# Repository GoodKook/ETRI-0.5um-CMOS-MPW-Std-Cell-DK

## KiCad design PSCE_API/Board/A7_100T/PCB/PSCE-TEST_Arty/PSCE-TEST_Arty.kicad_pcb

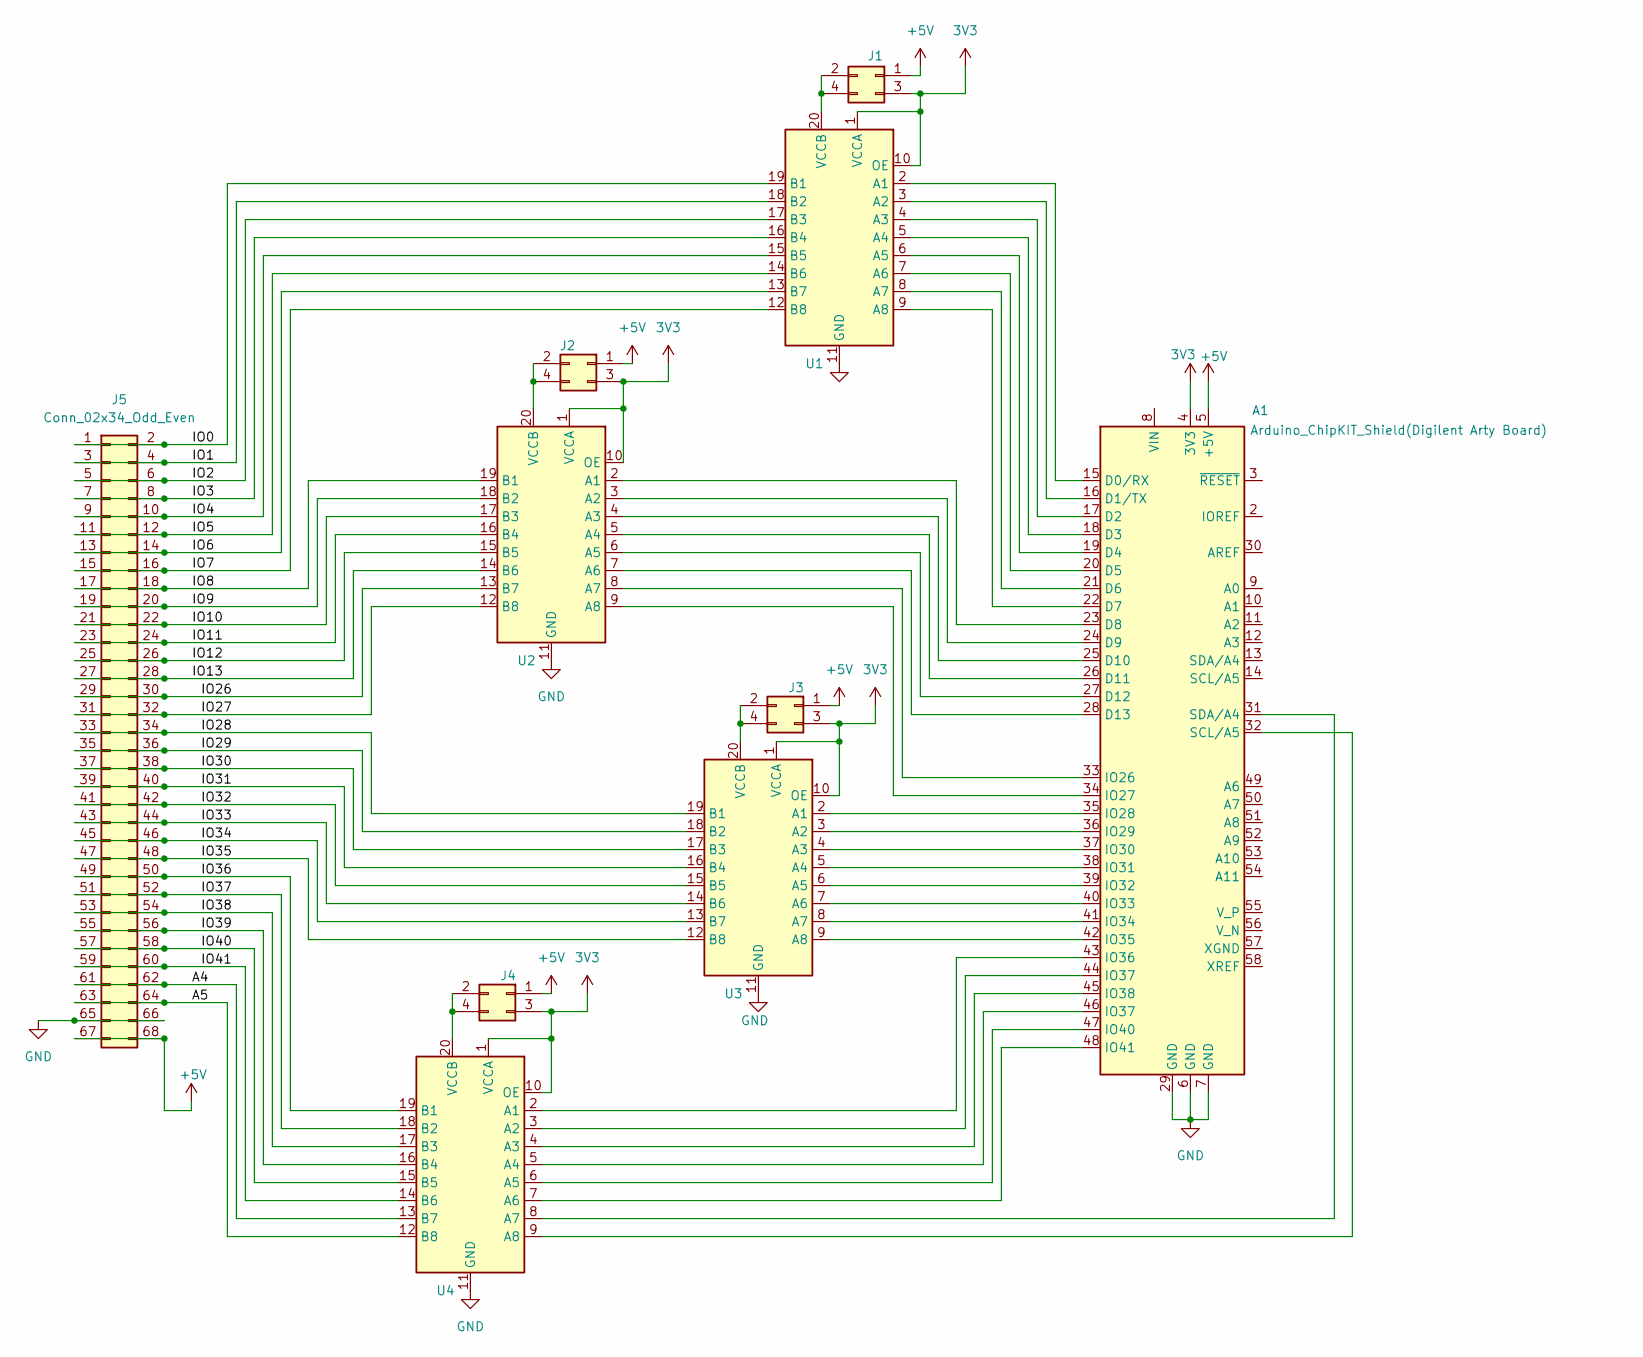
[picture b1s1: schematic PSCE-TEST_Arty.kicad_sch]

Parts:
A1: Arduino_ChipKIT_Shield(Digilent Arty Board); Arduino_ChipKIT_Shield
J1, J2, J3, J4: Conn_02x02_Odd_Even; PinHeader_2x02_P2.54mm_Vertical
J5: Conn_02x34_Odd_Even; PinHeader_2x34_P2.54mm_Vertical
U1, U2, U3, U4: Level_Shifter_Module_HW-221

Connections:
3V3: A1.4 (3V3), J1.3, J2.3, J3.3, J4.3, U1.1 (VCCA), U1.10 (OE), U2.1 (VCCA), U2.10 (OE), U3.1 (VCCA), U3.10 (OE), U4.1 (VCCA), U4.10 (OE)
+5V: A1.5 (+5V), J1.1, J2.1, J3.1, J4.1, J5.67, J5.68
/A4: J5.61, J5.62, U4.13 (B7)
/A5: J5.63, J5.64, U4.12 (B8)
/IO0: J5.1, J5.2, U1.19 (B1)
/IO1: J5.3, J5.4, U1.18 (B2)
/IO2: J5.5, J5.6, U1.17 (B3)
/IO3: J5.7, J5.8, U1.16 (B4)
/IO4: J5.9, J5.10, U1.15 (B5)
/IO5: J5.11, J5.12, U1.14 (B6)
/IO6: J5.13, J5.14, U1.13 (B7)
/IO7: J5.15, J5.16, U1.12 (B8)
/IO8: J5.17, J5.18, U2.19 (B1)
/IO9: J5.19, J5.20, U2.18 (B2)
/IO10: J5.21, J5.22, U2.17 (B3)
/IO11: J5.23, J5.24, U2.16 (B4)
/IO12: J5.25, J5.26, U2.15 (B5)
/IO13: J5.27, J5.28, U2.14 (B6)
/IO26: J5.29, J5.30, U2.13 (B7)
/IO27: J5.31, J5.32, U2.12 (B8)
/IO28: J5.33, J5.34, U3.19 (B1)
/IO29: J5.35, J5.36, U3.18 (B2)
/IO30: J5.37, J5.38, U3.17 (B3)
/IO31: J5.39, J5.40, U3.16 (B4)
/IO32: J5.41, J5.42, U3.15 (B5)
/IO33: J5.43, J5.44, U3.14 (B6)
/IO34: J5.45, J5.46, U3.13 (B7)
/IO35: J5.47, J5.48, U3.12 (B8)
/IO36: J5.49, J5.50, U4.19 (B1)
/IO37: J5.51, J5.52, U4.18 (B2)
/IO38: J5.53, J5.54, U4.17 (B3)
/IO39: J5.55, J5.56, U4.16 (B4)
/IO40: J5.57, J5.58, U4.15 (B5)
/IO41: J5.59, J5.60, U4.14 (B6)
GND: A1.6 (GND), A1.7 (GND), A1.29 (GND), J5.65, J5.66, U1.11 (GND), U2.11 (GND), U3.11 (GND), U4.11 (GND)
unnamed: A1.15 (D0/RX), U1.2 (A1)
unnamed: A1.16 (D1/TX), U1.3 (A2)
unnamed: A1.17 (D2), U1.4 (A3)
unnamed: A1.18 (D3), U1.5 (A4)
unnamed: A1.19 (D4), U1.6 (A5)
unnamed: A1.20 (D5), U1.7 (A6)
unnamed: A1.21 (D6), U1.8 (A7)
unnamed: A1.22 (D7), U1.9 (A8)
unnamed: A1.23 (D8), U2.2 (A1)
unnamed: A1.24 (D9), U2.3 (A2)
unnamed: A1.25 (D10), U2.4 (A3)
unnamed: A1.26 (D11), U2.5 (A4)
unnamed: A1.27 (D12), U2.6 (A5)
unnamed: A1.28 (D13), U2.7 (A6)
unnamed: A1.33 (IO26), U2.8 (A7)
unnamed: A1.34 (IO27), U2.9 (A8)
unnamed: A1.35 (IO28), U3.2 (A1)
unnamed: A1.36 (IO29), U3.3 (A2)
unnamed: A1.37 (IO30), U3.4 (A3)
unnamed: A1.38 (IO31), U3.5 (A4)
unnamed: A1.39 (IO32), U3.6 (A5)
unnamed: A1.40 (IO33), U3.7 (A6)
unnamed: A1.41 (IO34), U3.8 (A7)
unnamed: A1.42 (IO35), U3.9 (A8)
unnamed: A1.43 (IO36), U4.2 (A1)
unnamed: A1.45 (IO38), U4.4 (A3)
unnamed: A1.47 (IO40), U4.6 (A5)
unnamed: A1.48 (IO41), U4.7 (A6)
unnamed: J1.2, J1.4, U1.20 (VCCB)
unnamed: J2.2, J2.4, U2.20 (VCCB)
unnamed: J3.2, J3.4, U3.20 (VCCB)
unnamed: J4.2, J4.4, U4.20 (VCCB)
unnamed: A1.44 (IO37), U4.3 (A2)
unnamed: A1.46 (IO37), U4.5 (A4)
unnamed: A1.31 (SDA/A4), U4.8 (A7)
unnamed: A1.32 (SCL/A5), U4.9 (A8)

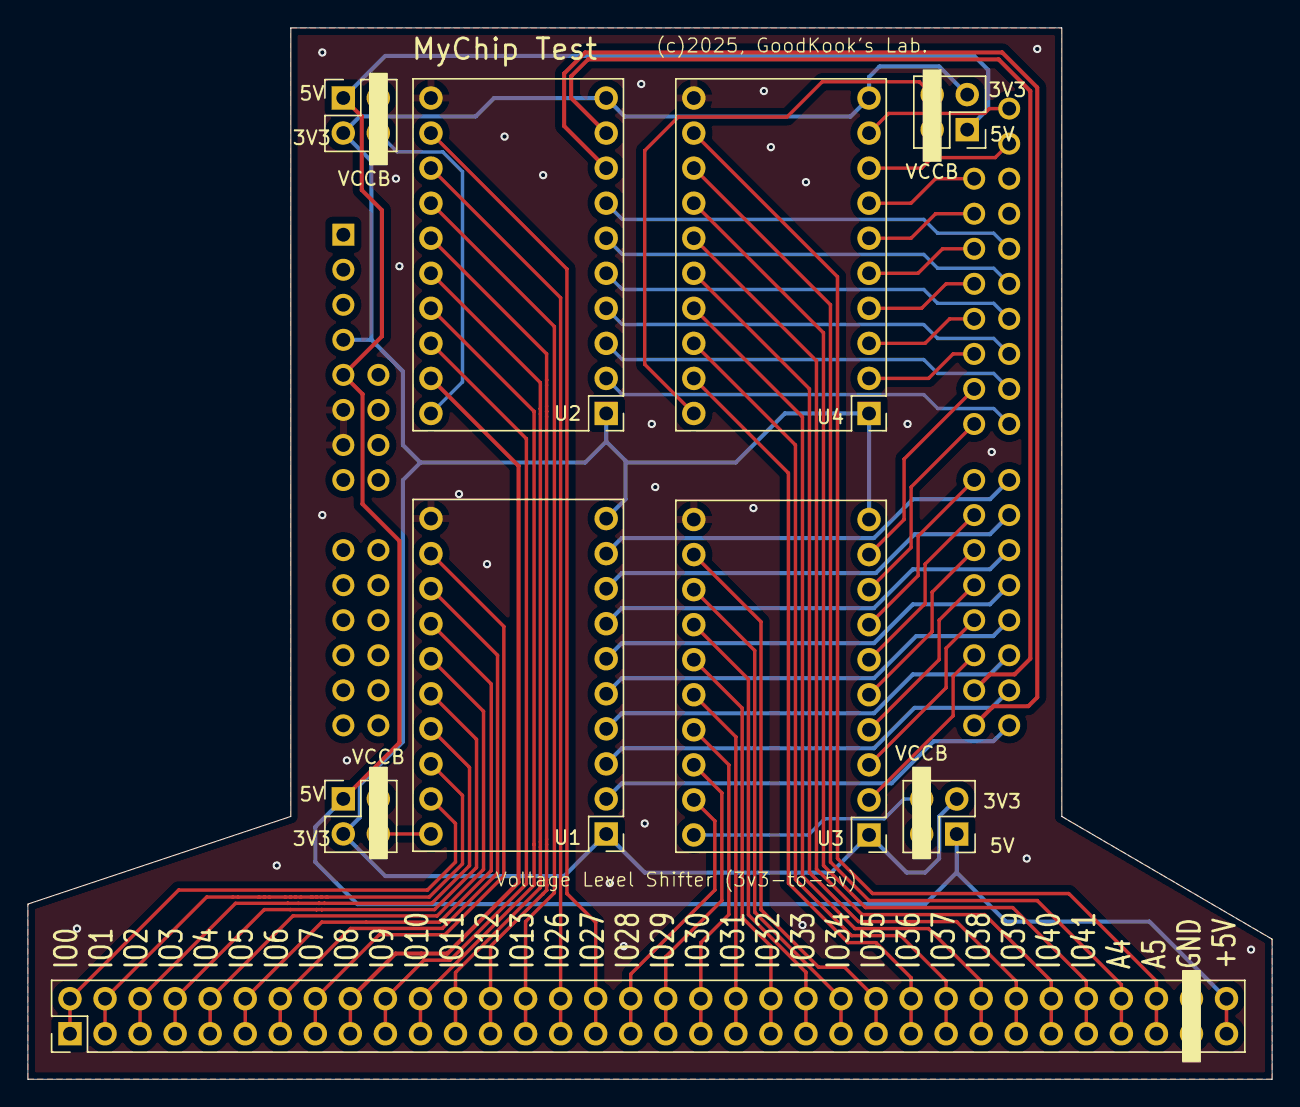
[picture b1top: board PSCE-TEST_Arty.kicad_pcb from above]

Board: 2 copper layers, 90.2 x 76.2 mm, 10 parts (0 on the bottom side), 71 nets.

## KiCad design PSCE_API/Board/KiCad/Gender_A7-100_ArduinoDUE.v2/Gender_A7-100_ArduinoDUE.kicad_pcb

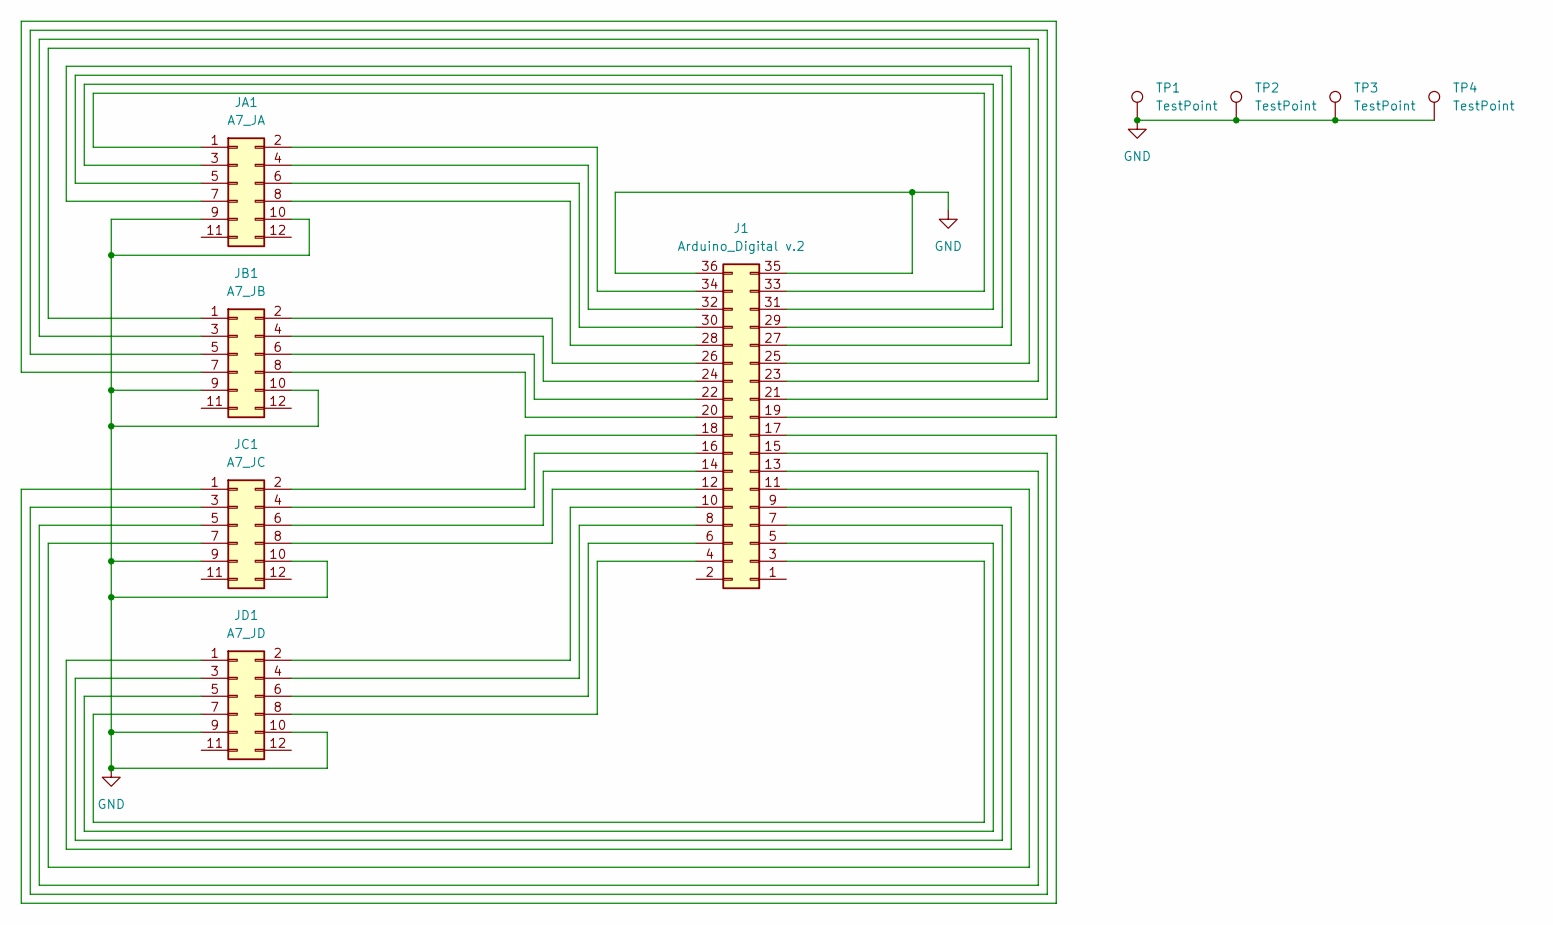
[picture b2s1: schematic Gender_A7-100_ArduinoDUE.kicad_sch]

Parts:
J1: Arduino_Digital v.2; PinHeader_2x18_P2.54mm_Vertical
JA1: A7_JA; PinHeader_2x06_P2.54mm_Vertical
JB1: A7_JB; PinHeader_2x06_P2.54mm_Vertical
JC1: A7_JC; PinHeader_2x06_P2.54mm_Vertical
JD1: A7_JD; PinHeader_2x06_P2.54mm_Vertical
TP1, TP2, TP4: TestPoint; TestPoint_Plated_Hole_D4.0mm
TP3: TestPoint; TestPoint_Bridge_Pitch7.62mm_Drill1.3mm

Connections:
GND: J1.35, J1.36, JA1.9, JA1.10, JB1.9, JB1.10, JC1.9, JC1.10, JD1.9, JD1.10, TP1.1, TP2.1, TP3.1, TP4.1
unnamed: J1.3, JD1.7
unnamed: J1.4, JD1.8
unnamed: J1.5, JD1.5
unnamed: J1.6, JD1.6
unnamed: J1.7, JD1.3
unnamed: J1.8, JD1.4
unnamed: J1.9, JD1.1
unnamed: J1.10, JD1.2
unnamed: J1.11, JC1.7
unnamed: J1.12, JC1.8
unnamed: J1.13, JC1.5
unnamed: J1.14, JC1.6
unnamed: J1.15, JC1.3
unnamed: J1.16, JC1.4
unnamed: J1.17, JC1.1
unnamed: J1.18, JC1.2
unnamed: J1.19, JB1.7
unnamed: J1.20, JB1.8
unnamed: J1.21, JB1.5
unnamed: J1.22, JB1.6
unnamed: J1.23, JB1.3
unnamed: J1.24, JB1.4
unnamed: J1.25, JB1.1
unnamed: J1.26, JB1.2
unnamed: J1.27, JA1.7
unnamed: J1.28, JA1.8
unnamed: J1.29, JA1.5
unnamed: J1.30, JA1.6
unnamed: J1.31, JA1.3
unnamed: J1.32, JA1.4
unnamed: J1.33, JA1.1
unnamed: J1.34, JA1.2

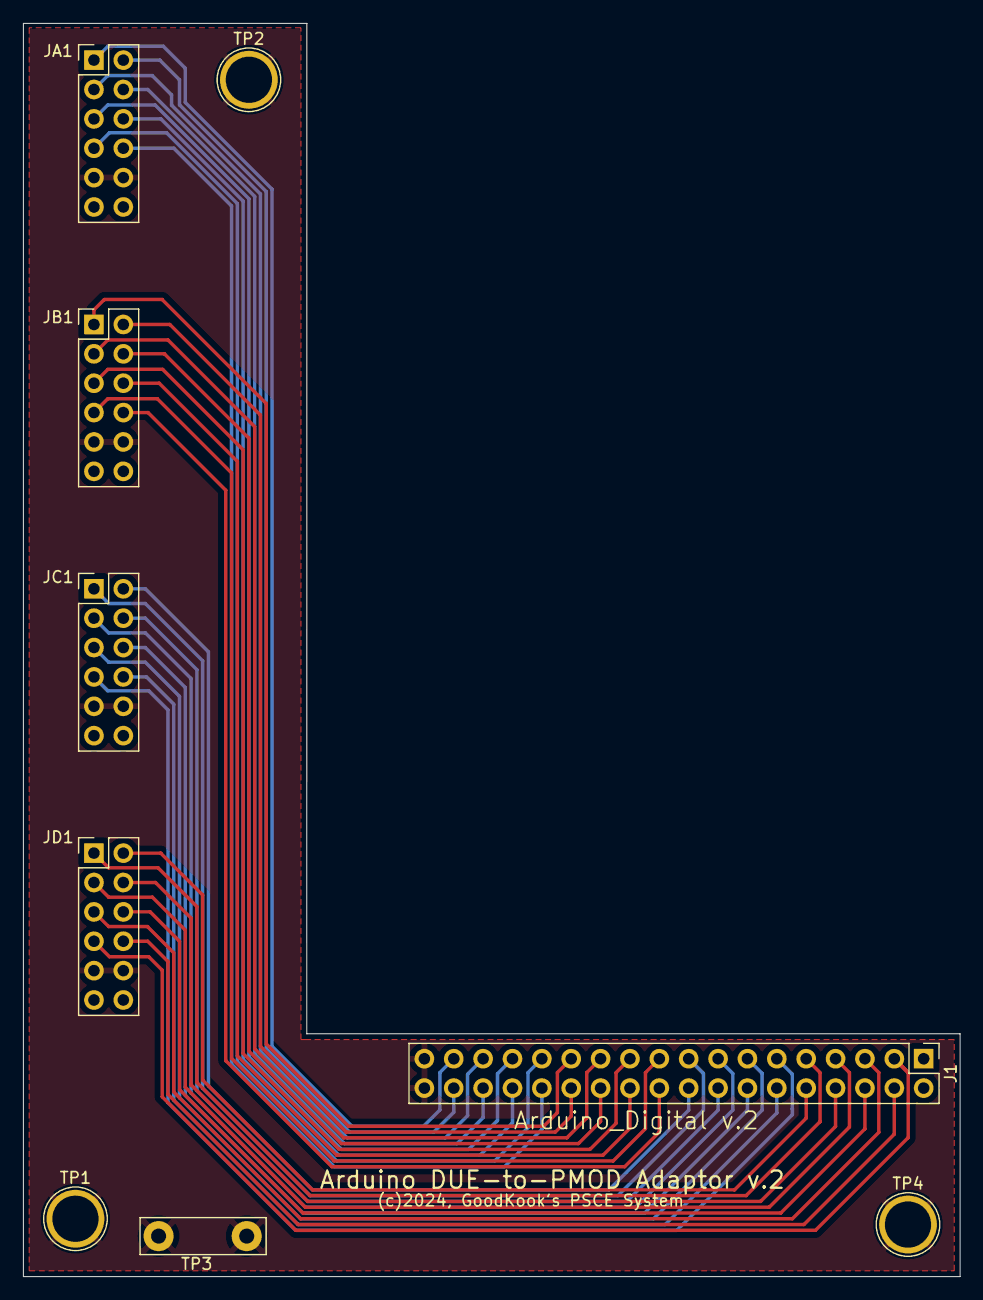
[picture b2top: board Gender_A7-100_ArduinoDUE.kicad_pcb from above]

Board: 2 copper layers, 81.0 x 108.4 mm, 9 parts (0 on the bottom side), 33 nets.

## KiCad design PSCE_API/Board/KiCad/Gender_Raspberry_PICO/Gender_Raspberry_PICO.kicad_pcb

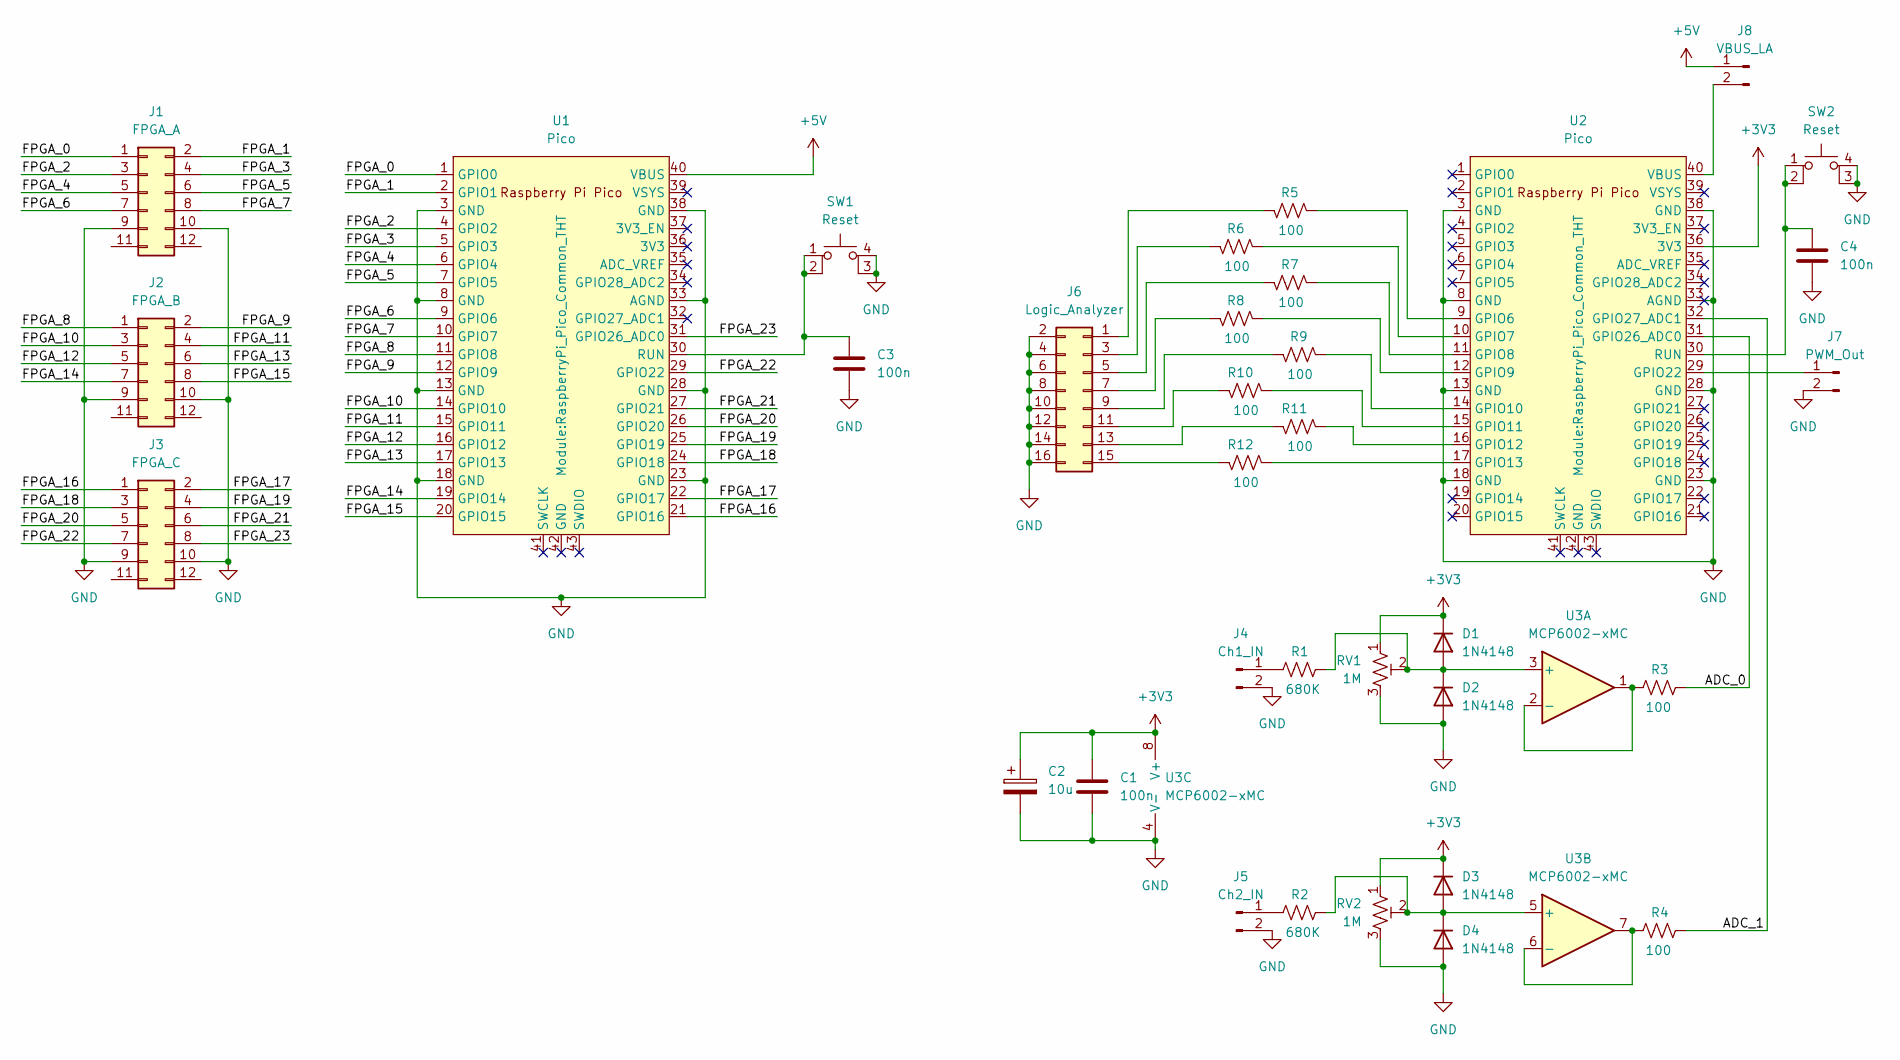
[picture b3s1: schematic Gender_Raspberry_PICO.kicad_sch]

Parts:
C1, C3, C4: 100n; C_Disc_D3.8mm_W2.6mm_P2.50mm
C2: 10u; CP_Radial_Tantal_D9.0mm_P2.50mm
D1, D2, D3, D4: 1N4148; D_DO-35_SOD27_P7.62mm_Horizontal
J1: FPGA_A; PinHeader_2x06_P2.54mm_Vertical
J2: FPGA_B; PinHeader_2x06_P2.54mm_Vertical
J3: FPGA_C; PinHeader_2x06_P2.54mm_Vertical
J4: Ch1_IN; PinHeader_2x01_P2.54mm_Vertical
J5: Ch2_IN; PinHeader_2x01_P2.54mm_Vertical
J6: Logic_Analyzer; PinHeader_2x08_P2.54mm_Vertical
J7: PWM_Out; PinHeader_2x01_P2.54mm_Vertical
J8: VBUS_LA; PinHeader_2x01_P2.54mm_Vertical
R1, R2: 680K; R_Axial_DIN0204_L3.6mm_D1.6mm_P7.62mm_Horizontal
R3, R4, R5, R6, R7, R8, R9, R10, R11, R12: 100; R_Axial_DIN0204_L3.6mm_D1.6mm_P7.62mm_Horizontal
RV1, RV2: 1M; Potentiometer_Runtron_RM-065_Vertical
SW1, SW2: Reset; SW_PUSH_6mm_H9.5mm
U1, U2: Pico; RaspberryPi_Pico_Common_THT
U3: MCP6002-xMC; DIP-8_W10.16mm_LongPads

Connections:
+3V3: C1.1, C2.1, D1.1 (K), D3.1 (K), RV1.1, RV2.1, U2.36 (3V3), U3.8 (V+)
+5V: J8.1, U1.40 (VBUS)
/ADC_0: R3.1, U2.31 (GPIO26_ADC0)
/ADC_1: R4.1, U2.32 (GPIO27_ADC1)
/FPGA_0: J1.1, U1.1 (GPIO0)
/FPGA_1: J1.2, U1.2 (GPIO1)
/FPGA_2: J1.3, U1.4 (GPIO2)
/FPGA_3: J1.4, U1.5 (GPIO3)
/FPGA_4: J1.5, U1.6 (GPIO4)
/FPGA_5: J1.6, U1.7 (GPIO5)
/FPGA_6: J1.7, U1.9 (GPIO6)
/FPGA_7: J1.8, U1.10 (GPIO7)
/FPGA_8: J2.1, U1.11 (GPIO8)
/FPGA_9: J2.2, U1.12 (GPIO9)
/FPGA_10: J2.3, U1.14 (GPIO10)
/FPGA_11: J2.4, U1.15 (GPIO11)
/FPGA_12: J2.5, U1.16 (GPIO12)
/FPGA_13: J2.6, U1.17 (GPIO13)
/FPGA_14: J2.7, U1.19 (GPIO14)
/FPGA_15: J2.8, U1.20 (GPIO15)
/FPGA_16: J3.1, U1.21 (GPIO16)
/FPGA_17: J3.2, U1.22 (GPIO17)
/FPGA_18: J3.3, U1.24 (GPIO18)
/FPGA_19: J3.4, U1.25 (GPIO19)
/FPGA_20: J3.5, U1.26 (GPIO20)
/FPGA_21: J3.6, U1.27 (GPIO21)
/FPGA_22: J3.7, U1.29 (GPIO22)
/FPGA_23: J3.8, U1.31 (GPIO26_ADC0)
GND: C1.2, C2.2, C3.2, C4.2, D2.2 (A), D4.2 (A), J1.9, J1.10, J2.9, J2.10, J3.9, J3.10, J4.2, J5.2, J6.2, J6.4, J6.6, J6.8, J6.10, J6.12, J6.14, J6.16, J7.2, RV1.3, RV2.3, SW1.3 (K), SW1.4 (A), SW2.3 (K), SW2.4 (A), U1.3 (GND), U1.8 (GND), U1.13 (GND), U1.18 (GND), U1.23 (GND), U1.28 (GND), U1.33 (AGND), U1.38 (GND), U2.3 (GND), U2.8 (GND), U2.13 (GND), U2.18 (GND), U2.23 (GND), U2.28 (GND), U2.33 (AGND), U2.38 (GND), U3.4 (V-), U3.9 (V-)
unnamed: D1.2 (A), D2.1 (K), R1.1, RV1.2, U3.3 (+)
unnamed: D3.2 (A), D4.1 (K), R2.1, RV2.2, U3.5 (+)
unnamed: J4.1, R1.2
unnamed: J5.1, R2.2
unnamed: J6.1, R5.1
unnamed: J6.3, R6.1
unnamed: J6.5, R7.1
unnamed: J6.7, R8.1
unnamed: J6.9, R9.1
unnamed: J6.11, R10.1
unnamed: J6.13, R11.1
unnamed: J6.15, R12.1
unnamed: J7.1, U2.29 (GPIO22)
unnamed: J8.2, U2.40 (VBUS)
unnamed: C3.1, SW1.1, SW1.2, U1.30 (RUN)
unnamed: R5.2, U2.9 (GPIO6)
unnamed: R6.2, U2.10 (GPIO7)
unnamed: R7.2, U2.11 (GPIO8)
unnamed: R8.2, U2.12 (GPIO9)
unnamed: R9.2, U2.14 (GPIO10)
unnamed: R10.2, U2.15 (GPIO11)
unnamed: R11.2, U2.16 (GPIO12)
unnamed: R12.2, U2.17 (GPIO13)
unnamed: C4.1, SW2.1, SW2.2, U2.30 (RUN)
unnamed: R3.2, U3.1, U3.2 (-)
unnamed: R4.2, U3.6 (-), U3.7

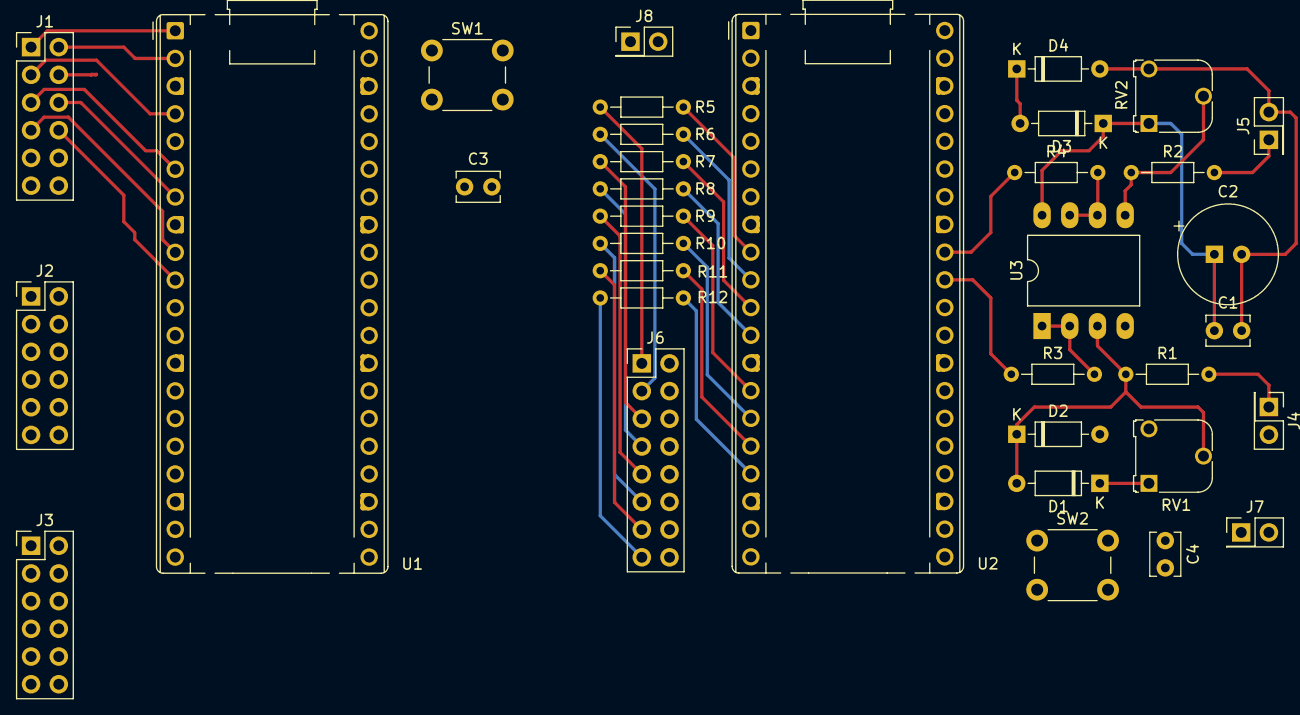
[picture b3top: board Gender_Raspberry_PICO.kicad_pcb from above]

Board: 2 copper layers, 35 parts (0 on the bottom side), 55 nets.

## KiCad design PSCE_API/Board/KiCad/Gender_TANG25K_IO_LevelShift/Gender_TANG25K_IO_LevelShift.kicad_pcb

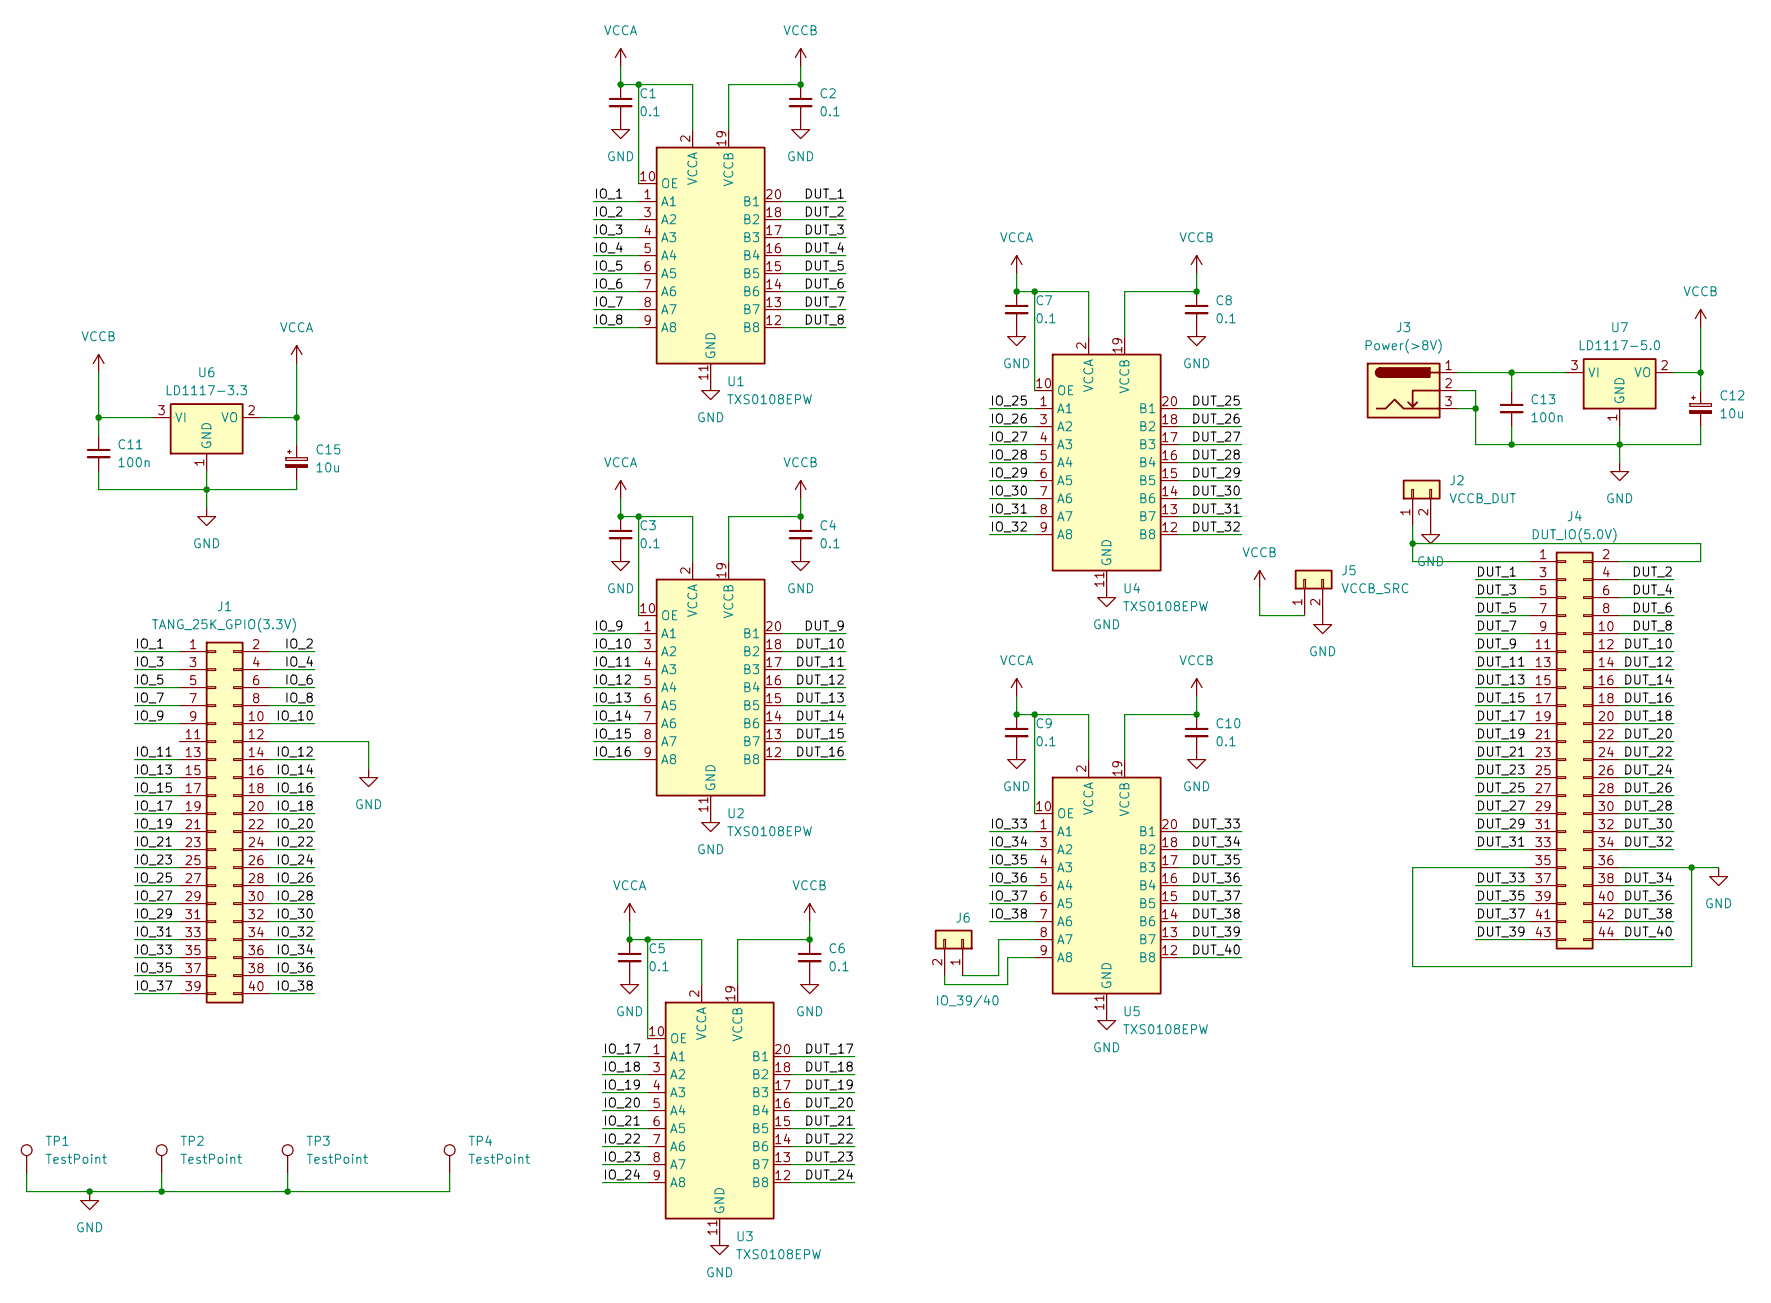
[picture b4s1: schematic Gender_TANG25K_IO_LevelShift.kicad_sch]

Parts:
C1, C2, C3, C4, C5, C6, C7, C8, C9, C10: 0.1; C_0805_2012Metric
C11, C13: 100n; C_0805_2012Metric
C12, C15: 10u; CP_Radial_D6.3mm_P2.50mm
J1: TANG_25K_GPIO(3.3V); PinHeader_2x20_P2.54mm_Vertical
J2: VCCB_DUT; PinHeader_1x02_P2.54mm_Vertical
J3: Power(>8V); BarrelJack_Kycon_KLDX-0202-xC_Horizontal
J4: DUT_IO(5.0V); PinHeader_2x22_P2.54mm_Vertical
J5: VCCB_SRC; PinHeader_1x02_P2.54mm_Vertical
J6: IO_39/40; PinHeader_1x02_P2.54mm_Vertical
TP1, TP2, TP3, TP4: TestPoint; TestPoint_Loop_D3.80mm_Drill2.8mm
U1, U2, U3, U4, U5: TXS0108EPW; TSSOP-20_4.4x6.5mm_P0.65mm
U6: LD1117-3.3; SOT-223-3_TabPin2
U7: LD1117-5.0; SOT-223-3_TabPin2

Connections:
/DUT_1: J4.3, U1.20 (B1)
/DUT_2: J4.4, U1.18 (B2)
/DUT_3: J4.5, U1.17 (B3)
/DUT_4: J4.6, U1.16 (B4)
/DUT_5: J4.7, U1.15 (B5)
/DUT_6: J4.8, U1.14 (B6)
/DUT_7: J4.9, U1.13 (B7)
/DUT_8: J4.10, U1.12 (B8)
/DUT_9: J4.11, U2.20 (B1)
/DUT_10: J4.12, U2.18 (B2)
/DUT_11: J4.13, U2.17 (B3)
/DUT_12: J4.14, U2.16 (B4)
/DUT_13: J4.15, U2.15 (B5)
/DUT_14: J4.16, U2.14 (B6)
/DUT_15: J4.17, U2.13 (B7)
/DUT_16: J4.18, U2.12 (B8)
/DUT_17: J4.19, U3.20 (B1)
/DUT_18: J4.20, U3.18 (B2)
/DUT_19: J4.21, U3.17 (B3)
/DUT_20: J4.22, U3.16 (B4)
/DUT_21: J4.23, U3.15 (B5)
/DUT_22: J4.24, U3.14 (B6)
/DUT_23: J4.25, U3.13 (B7)
/DUT_24: J4.26, U3.12 (B8)
/DUT_25: J4.27, U4.20 (B1)
/DUT_26: J4.28, U4.18 (B2)
/DUT_27: J4.29, U4.17 (B3)
/DUT_28: J4.30, U4.16 (B4)
/DUT_29: J4.31, U4.15 (B5)
/DUT_30: J4.32, U4.14 (B6)
/DUT_31: J4.33, U4.13 (B7)
/DUT_32: J4.34, U4.12 (B8)
/DUT_33: J4.37, U5.20 (B1)
/DUT_34: J4.38, U5.18 (B2)
/DUT_35: J4.39, U5.17 (B3)
/DUT_36: J4.40, U5.16 (B4)
/DUT_37: J4.41, U5.15 (B5)
/DUT_38: J4.42, U5.14 (B6)
/DUT_39: J4.43, U5.13 (B7)
/DUT_40: J4.44, U5.12 (B8)
/IO_1: J1.1, U1.1 (A1)
/IO_2: J1.2, U1.3 (A2)
/IO_3: J1.3, U1.4 (A3)
/IO_4: J1.4, U1.5 (A4)
/IO_5: J1.5, U1.6 (A5)
/IO_6: J1.6, U1.7 (A6)
/IO_7: J1.7, U1.8 (A7)
/IO_8: J1.8, U1.9 (A8)
/IO_9: J1.9, U2.1 (A1)
/IO_10: J1.10, U2.3 (A2)
/IO_11: J1.13, U2.4 (A3)
/IO_12: J1.14, U2.5 (A4)
/IO_13: J1.15, U2.6 (A5)
/IO_14: J1.16, U2.7 (A6)
/IO_15: J1.17, U2.8 (A7)
/IO_16: J1.18, U2.9 (A8)
/IO_17: J1.19, U3.1 (A1)
/IO_18: J1.20, U3.3 (A2)
/IO_19: J1.21, U3.4 (A3)
/IO_20: J1.22, U3.5 (A4)
/IO_21: J1.23, U3.6 (A5)
/IO_22: J1.24, U3.7 (A6)
/IO_23: J1.25, U3.8 (A7)
/IO_24: J1.26, U3.9 (A8)
/IO_25: J1.27, U4.1 (A1)
/IO_26: J1.28, U4.3 (A2)
/IO_27: J1.29, U4.4 (A3)
/IO_28: J1.30, U4.5 (A4)
/IO_29: J1.31, U4.6 (A5)
/IO_30: J1.32, U4.7 (A6)
/IO_31: J1.33, U4.8 (A7)
/IO_32: J1.34, U4.9 (A8)
/IO_33: J1.35, U5.1 (A1)
/IO_34: J1.36, U5.3 (A2)
/IO_35: J1.37, U5.4 (A3)
/IO_36: J1.38, U5.5 (A4)
/IO_37: J1.39, U5.6 (A5)
/IO_38: J1.40, U5.7 (A6)
GND: C1.2, C2.2, C3.2, C4.2, C5.2, C6.2, C7.2, C8.2, C9.2, C10.2, C11.2, C12.2, C13.2, C15.2, J1.12, J2.2, J3.2, J3.3, J4.35, J4.36, J5.2, TP1.1, TP2.1, TP3.1, TP4.1, U1.11 (GND), U2.11 (GND), U3.11 (GND), U4.11 (GND), U5.11 (GND), U6.1 (GND), U7.1 (GND)
unnamed: J2.1, J4.1, J4.2
unnamed: J6.1, U5.8 (A7)
unnamed: J6.2, U5.9 (A8)
unnamed: C13.1, J3.1, U7.3 (VI)
VCCA: C1.1, C3.1, C5.1, C7.1, C9.1, C15.1, U1.2 (VCCA), U1.10 (OE), U2.2 (VCCA), U2.10 (OE), U3.2 (VCCA), U3.10 (OE), U4.2 (VCCA), U4.10 (OE), U5.2 (VCCA), U5.10 (OE), U6.2 (VO)
VCCB: C2.1, C4.1, C6.1, C8.1, C10.1, C11.1, C12.1, J5.1, U1.19 (VCCB), U2.19 (VCCB), U3.19 (VCCB), U4.19 (VCCB), U5.19 (VCCB), U6.3 (VI), U7.2 (VO)

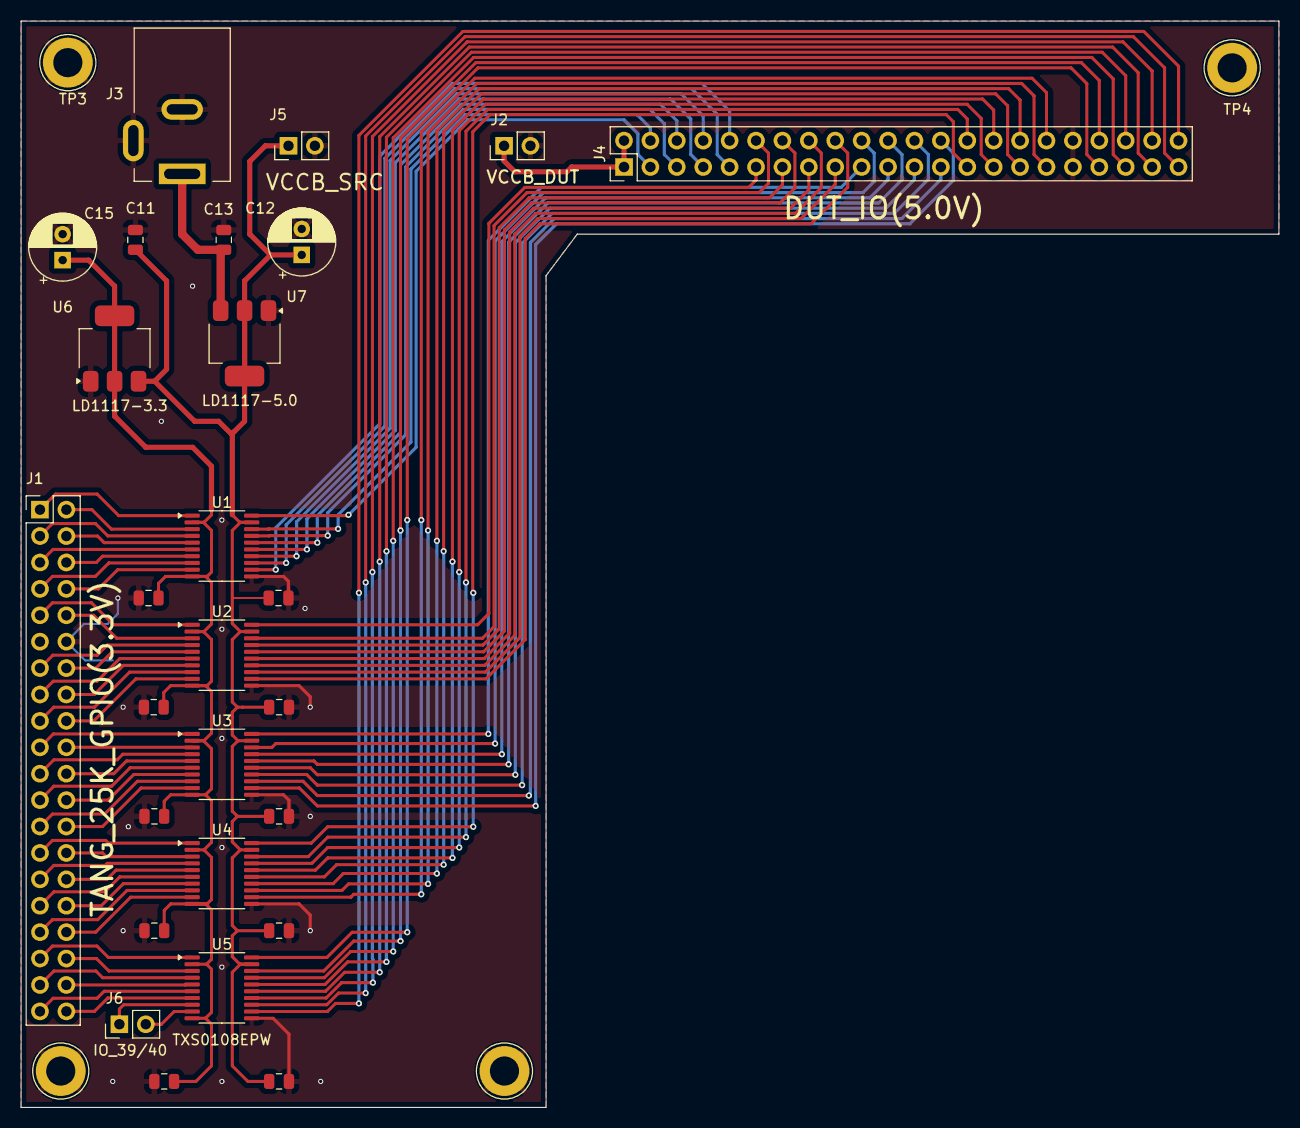
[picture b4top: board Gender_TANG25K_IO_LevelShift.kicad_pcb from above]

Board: 2 copper layers, 121.0 x 104.5 mm, 31 parts (0 on the bottom side), 85 nets.

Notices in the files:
PSCE_API/Board/KiCad/Gender_A7-100_ArduinoDUE.v2/Gender_A7-100_ArduinoDUE.kicad_pcb:
(c)2024, GoodKook's PSCE System
PSCE_API/Board/KiCad/PSCE-MI_ESP32-S3/PSCE-MI_ESP32-S3.kicad_pcb:
(c)2025, GoodKook Lab.
